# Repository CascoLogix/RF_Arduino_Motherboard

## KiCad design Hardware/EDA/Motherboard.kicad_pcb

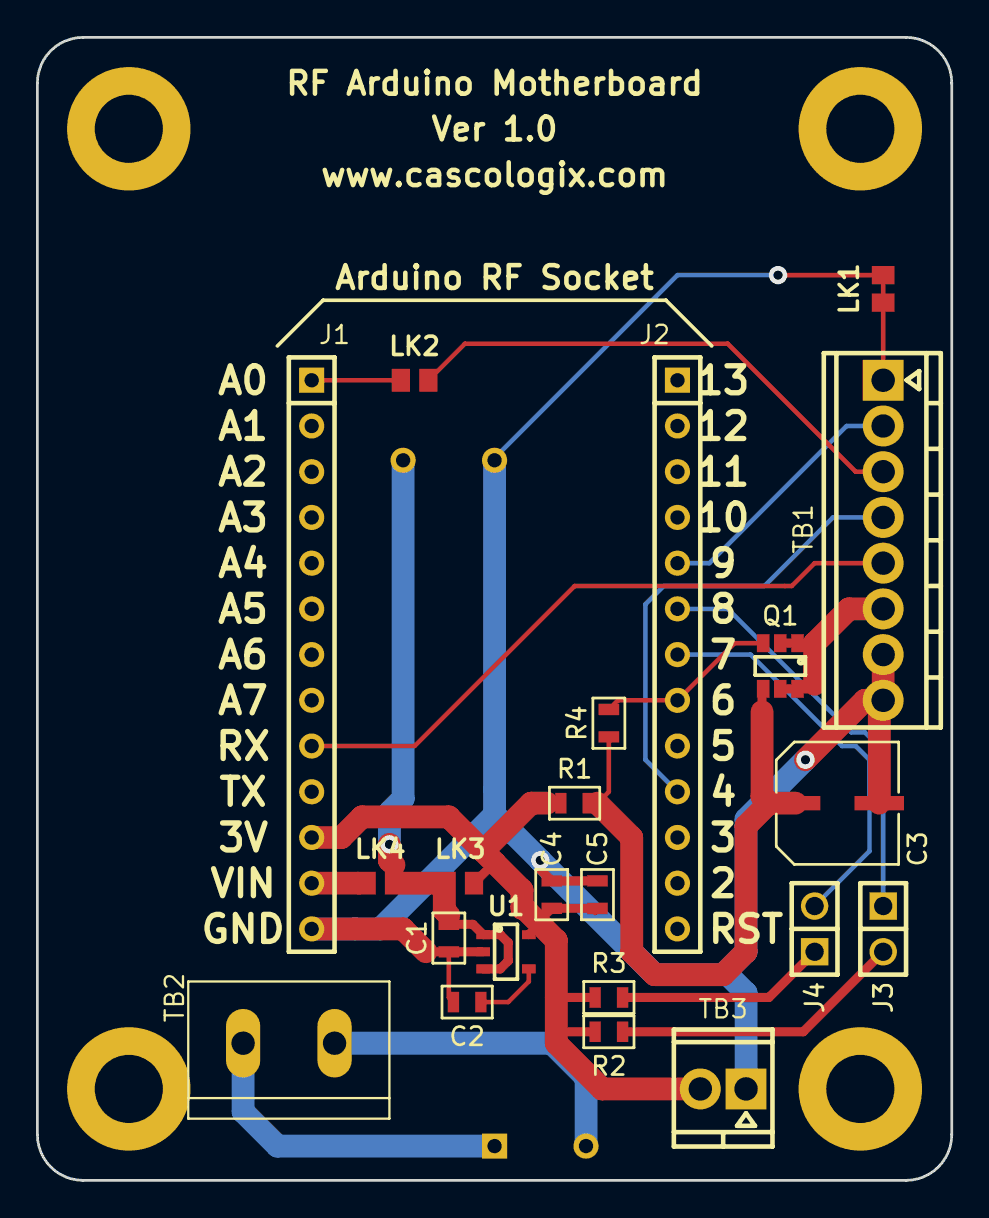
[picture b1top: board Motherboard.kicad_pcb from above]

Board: 2 copper layers, 50.8 x 63.5 mm, 27 parts (1 on the bottom side), 20 nets.

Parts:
C1, C2, C5: 1uF; 0603
C3: 100uF; CAP_F55
C4: 10uF; 0603
J1, J2: PPTC131LFBN-RC; HEADER_F_2.54MM_1R13P_ST_AU_PTH
J3, J4: DNP; HEADER_100MIL_1R2P_PTH
LK1: LK_NC; SOLDER_LINK_NC
LK2, LK3, LK4: SOLDER_LINK_NO
MH1, MH2, MH3, MH4: #6; MH_#6
PS1: DealXtreme 240410; AC_DC_Conv
Q1: DMP3105LVT; SOT23-6_SMT
R1: 100; R0603
R2, R3: DNP; R0603
R4: 47k; R0603
TB1: OSTVN_1x8; TB_100MIL_1R8P_PTH
TB2: OSTTC022162; CONN_2
TB3: OSTVN02A150; TB_100MIL_1R2P_PTH
U1: CAT6219-330TDGT3; SOT-23-5

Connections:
+3V3: C4.1, C5.1, J1.11, LK3.2, R1.2, R2.2, R3.2, TB3.2, U1.5
GND: C1.2, C2.2, C3.2, C4.2, C5.2, J1.13, LK1.2, PS1.4, TB1.7, TB1.8, TB3.1, U1.2
MAX_AN: J1.1, LK2.2
MAX_PW: J2.5, TB1.2
MAX_PWR: J2.8, Q1.3, R4.1
MAX_TRIG: J2.10, TB1.4
MAX_TX: J1.9, TB1.5
unnamed: C1.1, LK3.1, LK4.1, PS1.3, U1.1, U1.3
unnamed: C2.1, U1.4
unnamed: C3.1, Q1.4, R1.1, R4.2
unnamed: J2.6, J3.1
unnamed: J2.7, J4.2
unnamed: J3.2, R2.1
unnamed: J4.1, R3.1
unnamed: LK1.1, TB1.1
unnamed: LK2.1, TB1.3
unnamed: PS1.1, TB2.2
unnamed: PS1.2, TB2.1
unnamed: Q1.1, Q1.2, Q1.5, Q1.6, TB1.6
VIN: J1.12, LK4.2

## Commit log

2016-01-30 Initial Commit - Ordered from OSH Park
2016-01-30 Corrected filenames
